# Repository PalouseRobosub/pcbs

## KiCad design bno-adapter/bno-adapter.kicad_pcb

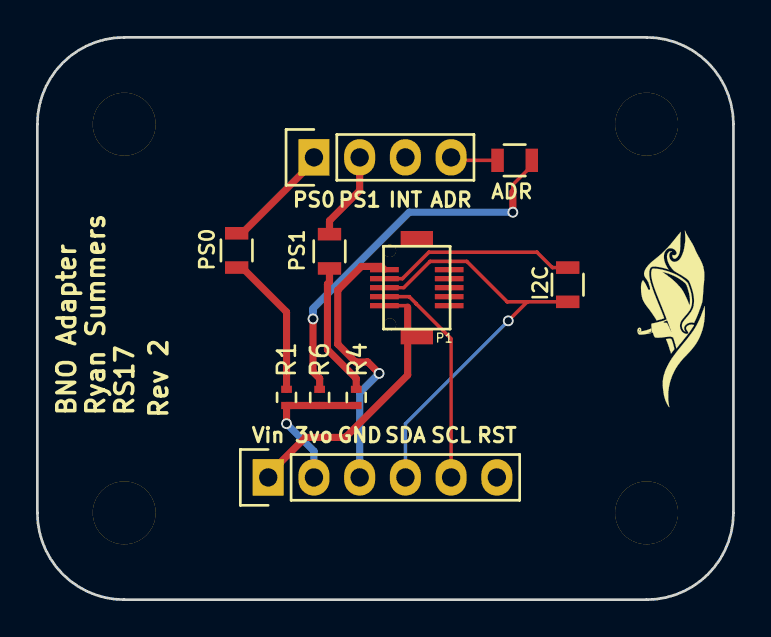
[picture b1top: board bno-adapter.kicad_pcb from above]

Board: 2 copper layers, 38.7 x 31.2 mm, 14 parts (0 on the bottom side), 12 nets.

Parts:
P1: Mezzanine-Header; 3mm-10pos-receptacle
P2: CONN_01X04; Pin_Header_Straight_1x04
P3: CONN_01X06; Pin_Header_Straight_1x06
P4, P5, P6, P7: Spacer; 3mm-spacer
R1, R4, R6: 10k; R_0402
R2, R3, R5, R7: 0; R_0805

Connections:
/3v0: P3.2, R1.1, R4.1, R6.1
/ADR: P2.4, R5.2
/PS0: P2.1, R2.2
/PS1: P2.2, R3.2
/RX/SDA_0: P1.5, P3.4, R7.2
/SCL: P1.3, P3.5
/SDA_1: P1.7, R7.1
/Vbus: P1.1, P3.1
GND: P1.9, P3.3
unnamed: R1.2, R2.1
unnamed: R3.1, R4.2
unnamed: R5.1, R6.2

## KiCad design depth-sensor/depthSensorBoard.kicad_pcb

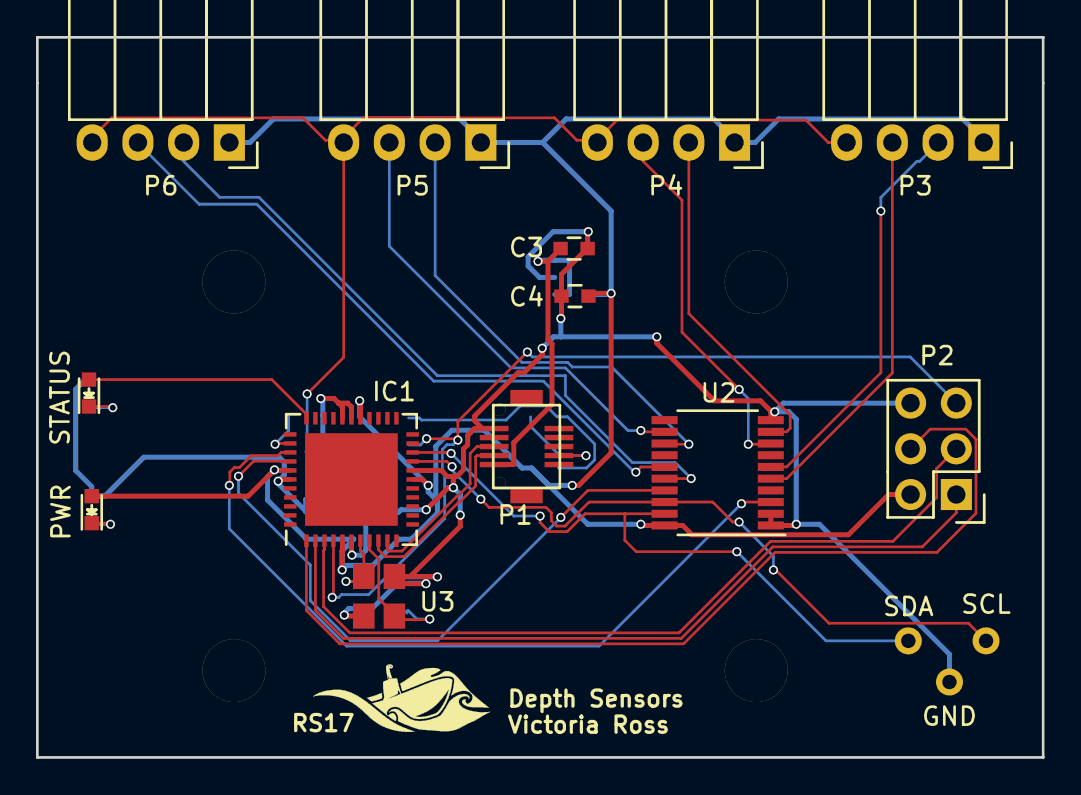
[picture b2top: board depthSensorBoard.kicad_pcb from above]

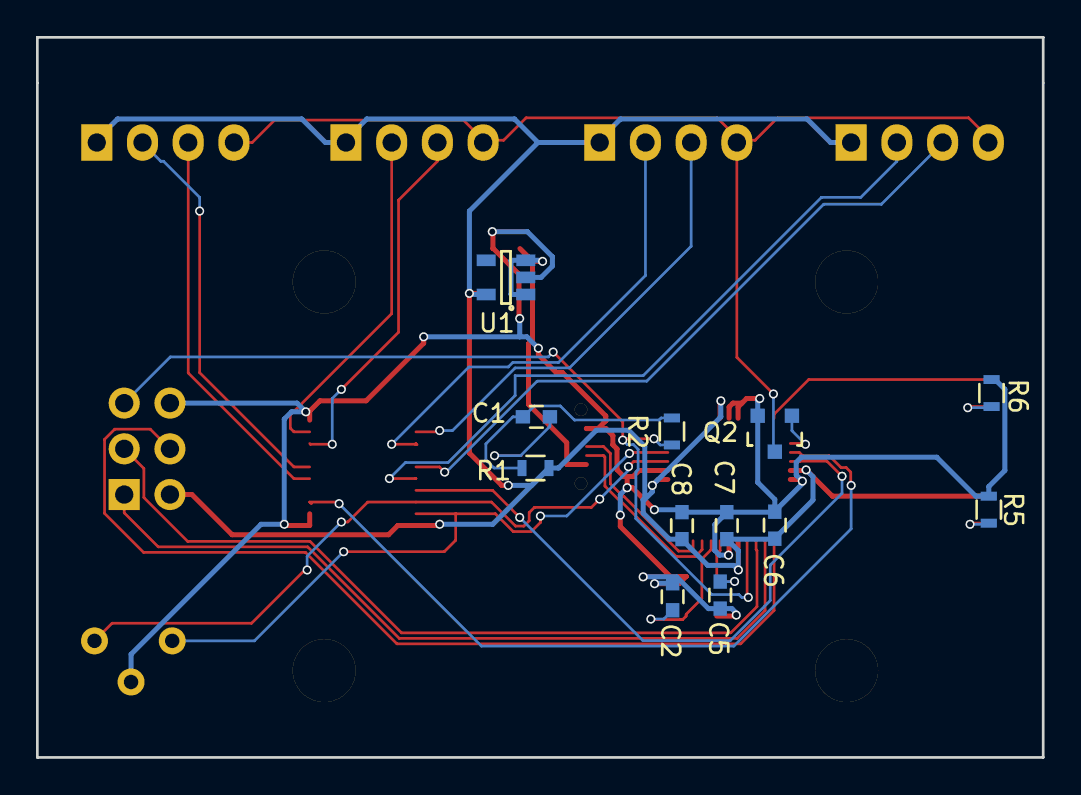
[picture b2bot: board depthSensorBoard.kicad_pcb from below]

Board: 2 copper layers, 55.9 x 40.0 mm, 32 parts (12 on the bottom side), 30 nets.

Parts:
C1: 100nF; C_0603
C2, C5: 18p; C_0603
C3, C4: 1µF; C_0603
C6, C7: 100n; C_0603
C8: 4.7u; C_0603
D3, D4: LED; LED_0603
IC1: ATMEGA1284P-M; QFN-44-1EP_7x7mm_Pitch0.5mm
M1, M2, M3, M4: MountingHole_3.5mm
P1: Mezzanine-Header; 3mm-10pos-receptacle
P2: CONN_02X03; Pin_Header_Straight_2x03
P3, P4, P5, P6: CONN_01X04; Socket_Strip_Angled_1x04
Q2: Q_NJFET_GSD; SOT-23
R1: 10k; R_0603
R2: 1k; R_0603
R5, R6: 65; R_0603
U1: AP2112; SOT-23-5
U2: TCA9545A; TSSOP-20_4.4x6.5mm_Pitch0.65mm
U3: TSX-3225; DFN-4
W1, W2, W3: TEST_1P; Measurement_Point_Round-TH_Small

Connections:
+3V3: C4.1, C6.1, C7.1, C8.1, D3.2, IC1.5, IC1.17, IC1.27, IC1.38, P2.2, P3.1, P4.1, P5.1, P6.1, R1.1, U1.5, U2.20
+5V: C3.1, P1.1, U1.1, U1.3
/ATMega1284p/MISO: IC1.2, P2.1
/ATMega1284p/MOSI: IC1.1, P2.4
/ATMega1284p/SCK: IC1.3, P2.3
/ATMega1284p/~RST: IC1.4, P2.5, R2.1
/DBG_LED: D4.2, IC1.33
/DTR: C1.2, P1.4
/Gate: IC1.35, Q2.1
/Rx_CPU: IC1.10, P1.5
/SCL: IC1.19, U2.18, W2.1
/SCL0: P3.2, U2.6
/SCL1: P4.2, U2.9
/SCL2: P5.2, U2.13
/SCL3: P6.2, U2.16
/SDA: IC1.20, U2.19, W1.1
/SDA0: P3.3, U2.5
/SDA1: P4.3, U2.8
/SDA2: P5.3, U2.12
/SDA3: P6.3, U2.15
/Tx_CPU: IC1.9, P1.3
/drn: P3.4, P4.4, P5.4, P6.4, Q2.3
/~INT: IC1.37, U2.17
/~RST: IC1.36, U2.3
GND: C2.2, C3.2, C4.2, C5.2, C6.2, C7.2, C8.2, IC1.6, IC1.18, IC1.28, IC1.29, IC1.39, P1.9, P2.6, Q2.2, R5.2, R6.2, U1.2, U2.1, U2.2, U2.10, U3.2, U3.4, W3.1
unnamed: C1.1, R1.2, R2.2
unnamed: C2.1, IC1.8, U3.3
unnamed: C5.1, IC1.7, U3.1
unnamed: D3.1, R5.1
unnamed: D4.1, R6.1

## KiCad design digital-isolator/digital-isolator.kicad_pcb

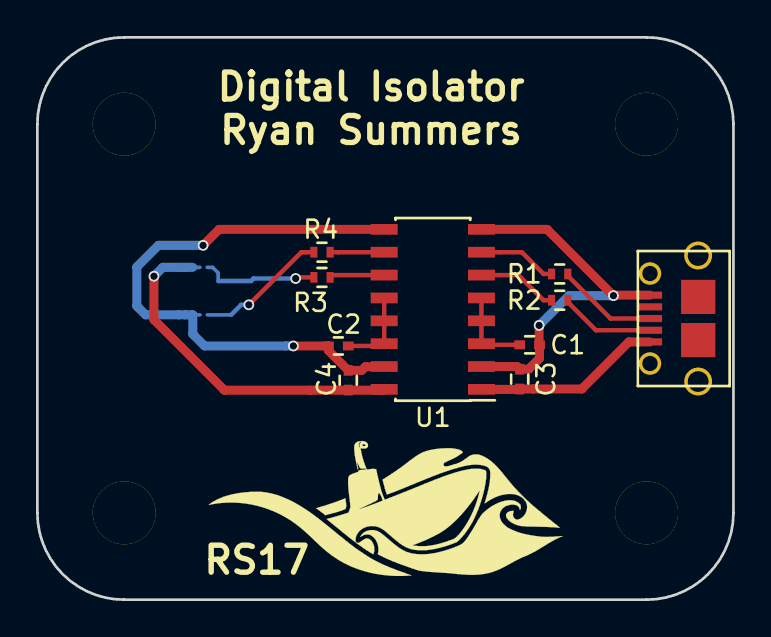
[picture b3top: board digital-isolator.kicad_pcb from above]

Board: 2 copper layers, 38.7 x 31.2 mm, 15 parts (1 on the bottom side), 14 nets.

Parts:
C1, C2, C3, C4: 100n; C_0402
P1: USB_OTG; USB-Micro-B-TH
P2: CONN_02X05; DF40C-10DS-Receptacle
P3, P4, P5, P6: CONN_01X01; 1.5mm-spacer
R1, R2, R3, R4: 24/1%; R_0402
U1: ADUM3160; SOIC-16_3.9x9.9mm_Pitch1.27mm

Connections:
+5V: C4.1, P2.1, P2.3, P2.5, P2.7, U1.16
/USB+: P2.10, R4.1
/USB-: P2.9, R3.1
/USB_H+: P1.3, R1.2
/USB_H-: P1.2, R2.2
/Vbus1: C3.1, P1.1, U1.1
/Vdd1: C1.1, U1.3, U1.4, U1.5
/Vdd2: C2.1, U1.12, U1.13, U1.14
GND: C1.2, C3.2, P1.5, U1.2, U1.8
GNDPWR: C2.2, C4.2, P2.2, P2.4, P2.6, P2.8, U1.9, U1.15
unnamed: R1.1, U1.7
unnamed: R2.1, U1.6
unnamed: R3.2, U1.11
unnamed: R4.2, U1.10
